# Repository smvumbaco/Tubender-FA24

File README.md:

# <PROJECT NAME>
<ADD BLURB ABOUT PROJECT>

## Directory Structure:
```
.
|
|───production  # contains files needed for final prototype
|   |
|   |───eCAD    # contains the KiCAD project
|   └───src     # contains the code needed for deployment
|
|───testing     # contains files relevant to testing components
|
└───README.md   # this file!
```

## Preferred Tools
- KiCAD 7 for PCB development
- Visual Studio Code / PlatformIO for code development
- Git CLI / GitHub Desktop for managing Git

## Branches
- Main branch contains all tested/verified work
- Development work is contained on separate branches

## References
- Schematics + Components (WIP)

## Practice Good Git Hygiene!
1. Only commit files you intended to change
2. Create branches for each feature
3. Check your branch before starting work
4. Pull frequently to avoid conflicts
5. Make Pull Requests when you are ready to merge into a larger branch

## Git Resources

* [Setting up Git](https://fanatical-colossus-434.notion.site/Git-Installation-and-Setup-d07b7d1ab5544424876f9fd3b4a0b312)
* [Intro to Git Crash Course](https://fanatical-colossus-434.notion.site/Crash-Course-Intro-to-Git-809641611da9478b8f9cca8fd97e49fe)

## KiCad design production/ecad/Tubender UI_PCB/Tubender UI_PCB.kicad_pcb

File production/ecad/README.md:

This is where all KiCAD stuff is stored

To make development and merging easier, a hierarchical design is suggested for schematics. This enables engineers to work on different sections of the schematicand minimize the amount of conflicts received.

`components` directory contains components utilized in this system

Please utilize whatever KiCAD version is requested by the lead. If you aren't sure which version, please ask your lead.

! Remember to only commit the `.kicad_sch`, `.kicad_pcb`, and `.kicad_pro` to this repository, everything else isn't needed to reconstruct the schematic on any KiCAD enabled machine

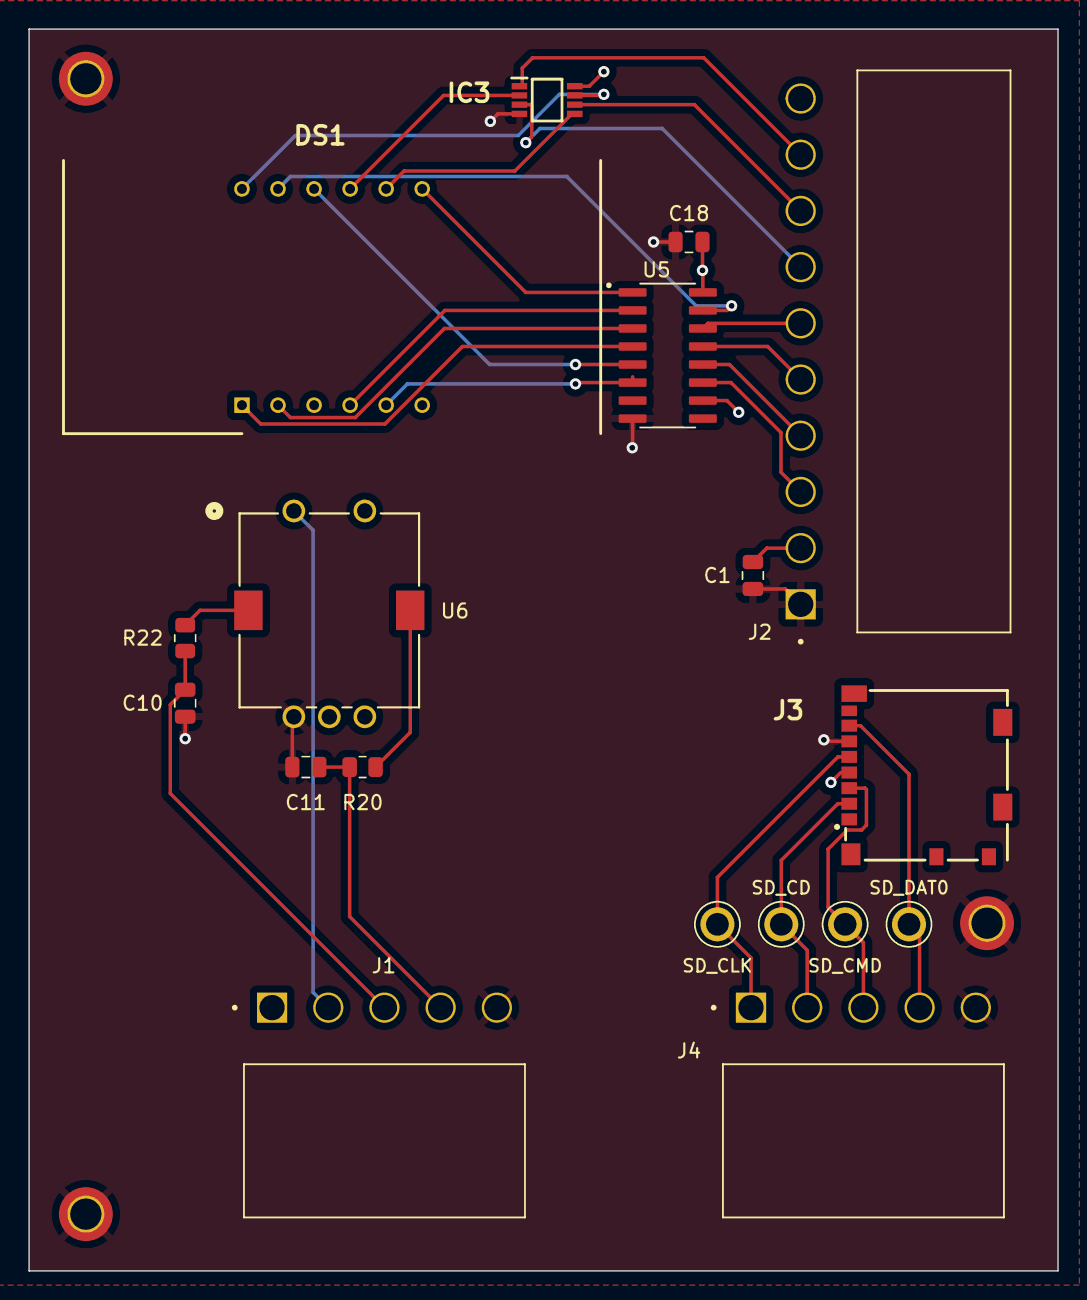
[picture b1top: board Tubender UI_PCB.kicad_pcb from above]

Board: 4 copper layers, 72.5 x 87.5 mm, 18 parts (0 on the bottom side), 29 nets.

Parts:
C1: 0.1u; C_0805_2012Metric
C10, C11: 0.01u; C_0805_2012Metric
C18: 0.1uF; C_0805_2012Metric
DS1: BC56-12EWA; DIPS1524W50P254L3760H835Q12N
IC3: SN74LVC1G29DCTR; SOP65P400X130-8N
J1, J4: 640387-5; TE_640387-5
J2: 1-640387-0; TE_1-640387-0
J3: 104031-0811; 1040310811
R20, R22: 10k; R_0805_2012Metric
SD_CD: 5006; KEYSTONE_5006
SD_CLK: 5006; KEYSTONE_5006
SD_CMD: 5006; KEYSTONE_5006
SD_DAT0: 5006; KEYSTONE_5006
U5: 74HC595; SOIC127P600X175-16N
U6: PEC11R-4215K-S0024; SW_PEC11R-4XXXK-SXXXX_BRN

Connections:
7-SEG_A0: IC3.3 (A0), J2.7
7-SEG_A1: IC3.6 (A1), J2.8
7-SEG_Gb: IC3.1 (~G), J2.9
7-SEG_OEb: J2.5, U5.13 (~OE)
7-SEG_RCLK: J2.4, U5.12 (RCLK)
7-SEG_SER: J2.6, U5.14 (SER)
7-SEG_SRCLK: J2.3, U5.11 (SRCLK)
+3V3: C1.1, J2.2, J3.4 (VDD), U5.10 (~SRCLR)
+5V: C18.1, IC3.8 (VCC), J1.1, J2.10, U5.16 (VCC), U6.2
DIAL_BUTTON: J1.2, U6.1
DIAL_CHANNEL_A: C10.1, J1.3, R22.2
DIAL_CHANNEL_B: C11.1, J1.4, R20.2
GND: C1.2, C10.2, C11.2, C18.2, IC3.4 (GND), J1.5, J2.1, J3.6 (VSS), J4.5, U5.8 (GND), U6.5 (C)
unnamed: DS1.11 (ANODE_A), U5.15 (QA)
unnamed: DS1.7 (ANODE_B), U5.1 (QB)
unnamed: DS1.4 (ANODE_C), U5.2 (QC)
unnamed: DS1.2 (ANODE_D), U5.3 (QD)
unnamed: DS1.1 (ANODE_E), U5.4 (QE)
unnamed: DS1.10 (ANODE_F), U5.5 (QF)
unnamed: DS1.5 (ANODE_G), U5.6 (QG)
unnamed: DS1.12 (COMMON_CATHODE_DIG1), IC3.7 (Y0)
unnamed: DS1.9 (COMMON_CATHODE_DIG2), IC3.2 (Y1)
unnamed: DS1.8 (COMMON_CATHODE_DIG_3), IC3.5 (Y2)
unnamed: R22.1, U6.3 (A)
unnamed: R20.1, U6.4 (B)
SD_CD: J3.2 (CD/DAT3), J4.2, SD_CD.TP
SD_CLK: J3.5 (CLK), J4.1, SD_CLK.TP
SD_CMD: J3.3 (CMD), J4.3, SD_CMD.TP
SD_DAT0: J3.7 (DAT0), J4.4, SD_DAT0.TP

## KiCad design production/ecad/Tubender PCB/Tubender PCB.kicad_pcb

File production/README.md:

# Production
This directory is for code/schematics/layouts that will be implemented in the final prototype.

> **_NOTE:_** If you have code to test out a component/subsystem, it should probably go into ```/testing```

## Directory Structure:
```
.
|───ecad    # contains any schematic/board development files
|
└───src     # contains any embedded code or important scripts
```

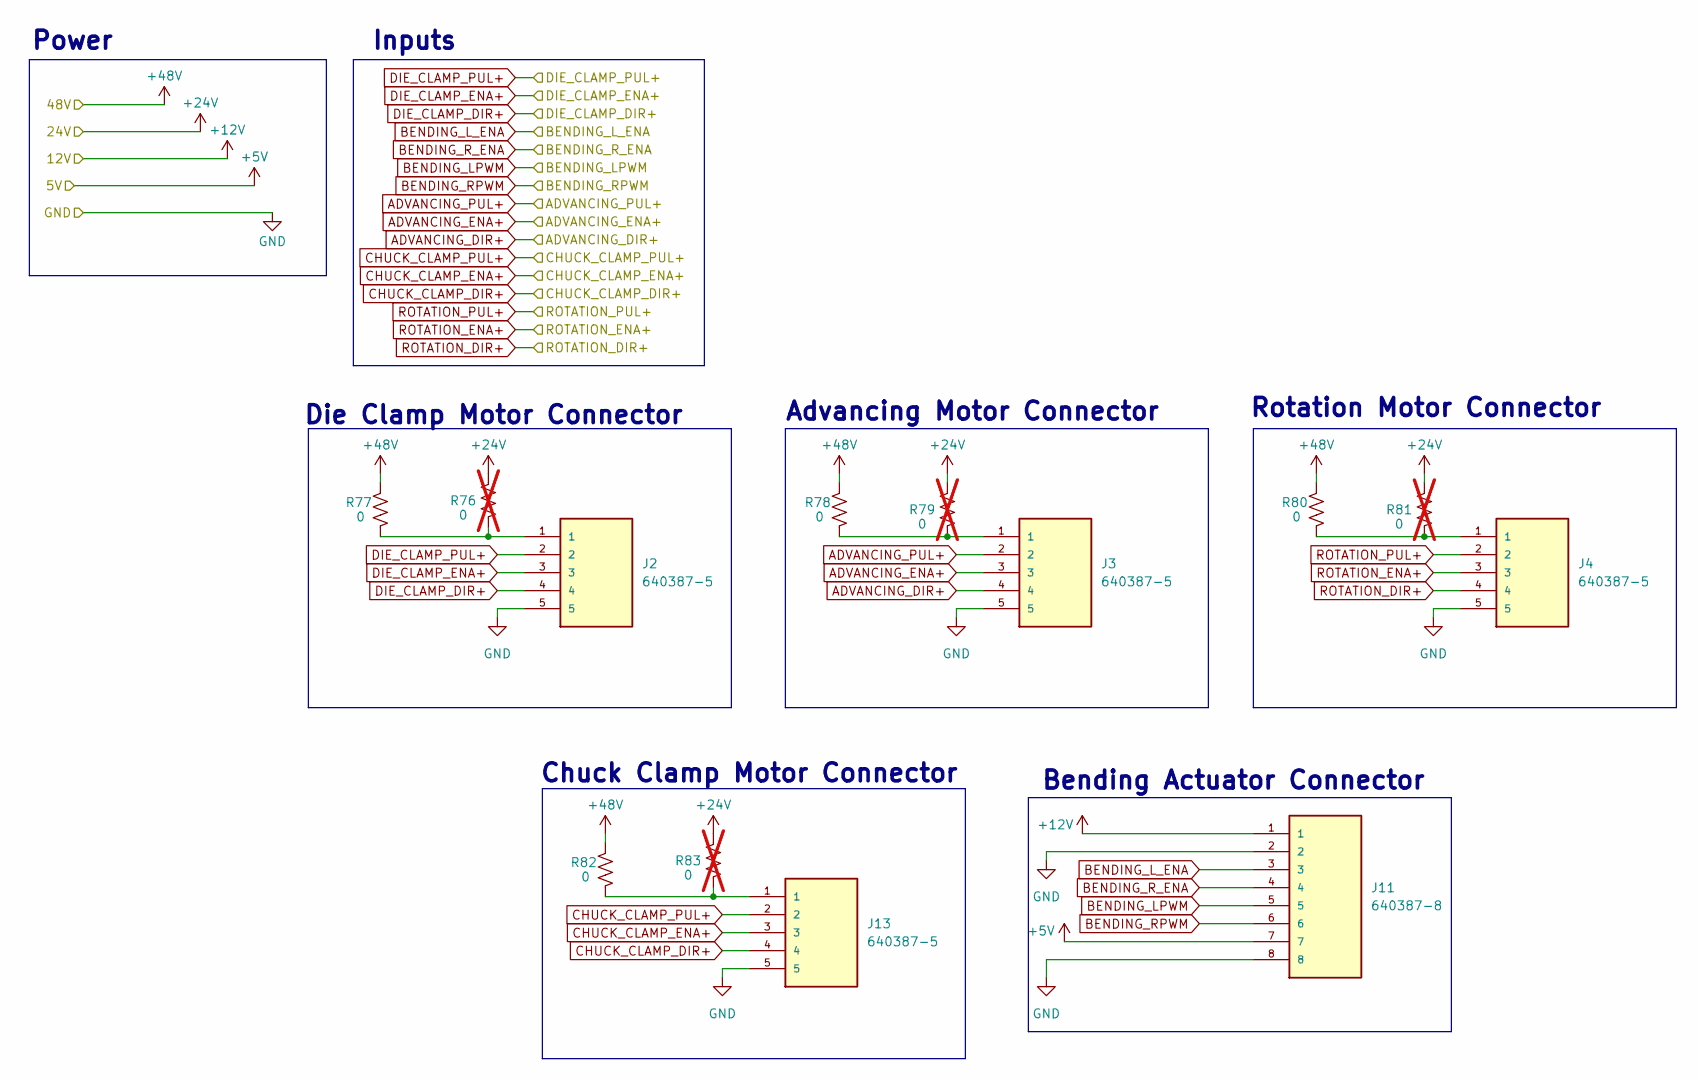
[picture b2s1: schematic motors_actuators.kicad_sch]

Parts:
J2, J3, J4, J13: 640387-5; TE_640387-5; PARTREV R
J11: 640387-8; TE_640387-8; PARTREV R
R76, R79, R81, R83: 0; R_0805_2012Metric; not fitted
R77, R78, R80, R82: 0; R_0805_2012Metric

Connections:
5V: J11.7; also elsewhere on the board
12V: J11.1; also elsewhere on the board
24V: R76.2, R79.2, R81.2, R83.2; also elsewhere on the board
48V: R77.2, R78.2, R80.2, R82.2; also elsewhere on the board
ADVANCING_DIR+: J3.4; also elsewhere on the board
ADVANCING_ENA+: J3.3; also elsewhere on the board
ADVANCING_PUL+: J3.2; also elsewhere on the board
BENDING_LPWM: J11.5; also elsewhere on the board
BENDING_L_ENA: J11.3; also elsewhere on the board
BENDING_RPWM: J11.6; also elsewhere on the board
BENDING_R_ENA: J11.4; also elsewhere on the board
CHUCK_CLAMP_DIR+: J13.4; also elsewhere on the board
CHUCK_CLAMP_ENA+: J13.3; also elsewhere on the board
CHUCK_CLAMP_PUL+: J13.2; also elsewhere on the board
DIE_CLAMP_DIR+: J2.4; also elsewhere on the board
DIE_CLAMP_ENA+: J2.3; also elsewhere on the board
DIE_CLAMP_PUL+: J2.2; also elsewhere on the board
GND: J2.5, J3.5, J4.5, J11.2, J11.8, J13.5; also elsewhere on the board
unnamed: J2.1, R76.1, R77.1
unnamed: J3.1, R78.1, R79.1
unnamed: J4.1, R80.1, R81.1
unnamed: J13.1, R82.1, R83.1
ROTATION_DIR+: J4.4; also elsewhere on the board
ROTATION_ENA+: J4.3; also elsewhere on the board
ROTATION_PUL+: J4.2; also elsewhere on the board

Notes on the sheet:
Chuck Clamp Motor Connector
Die Clamp Motor Connector
Bending Actuator Connector
Inputs
Advancing Motor Connector
Power
Rotation Motor Connector

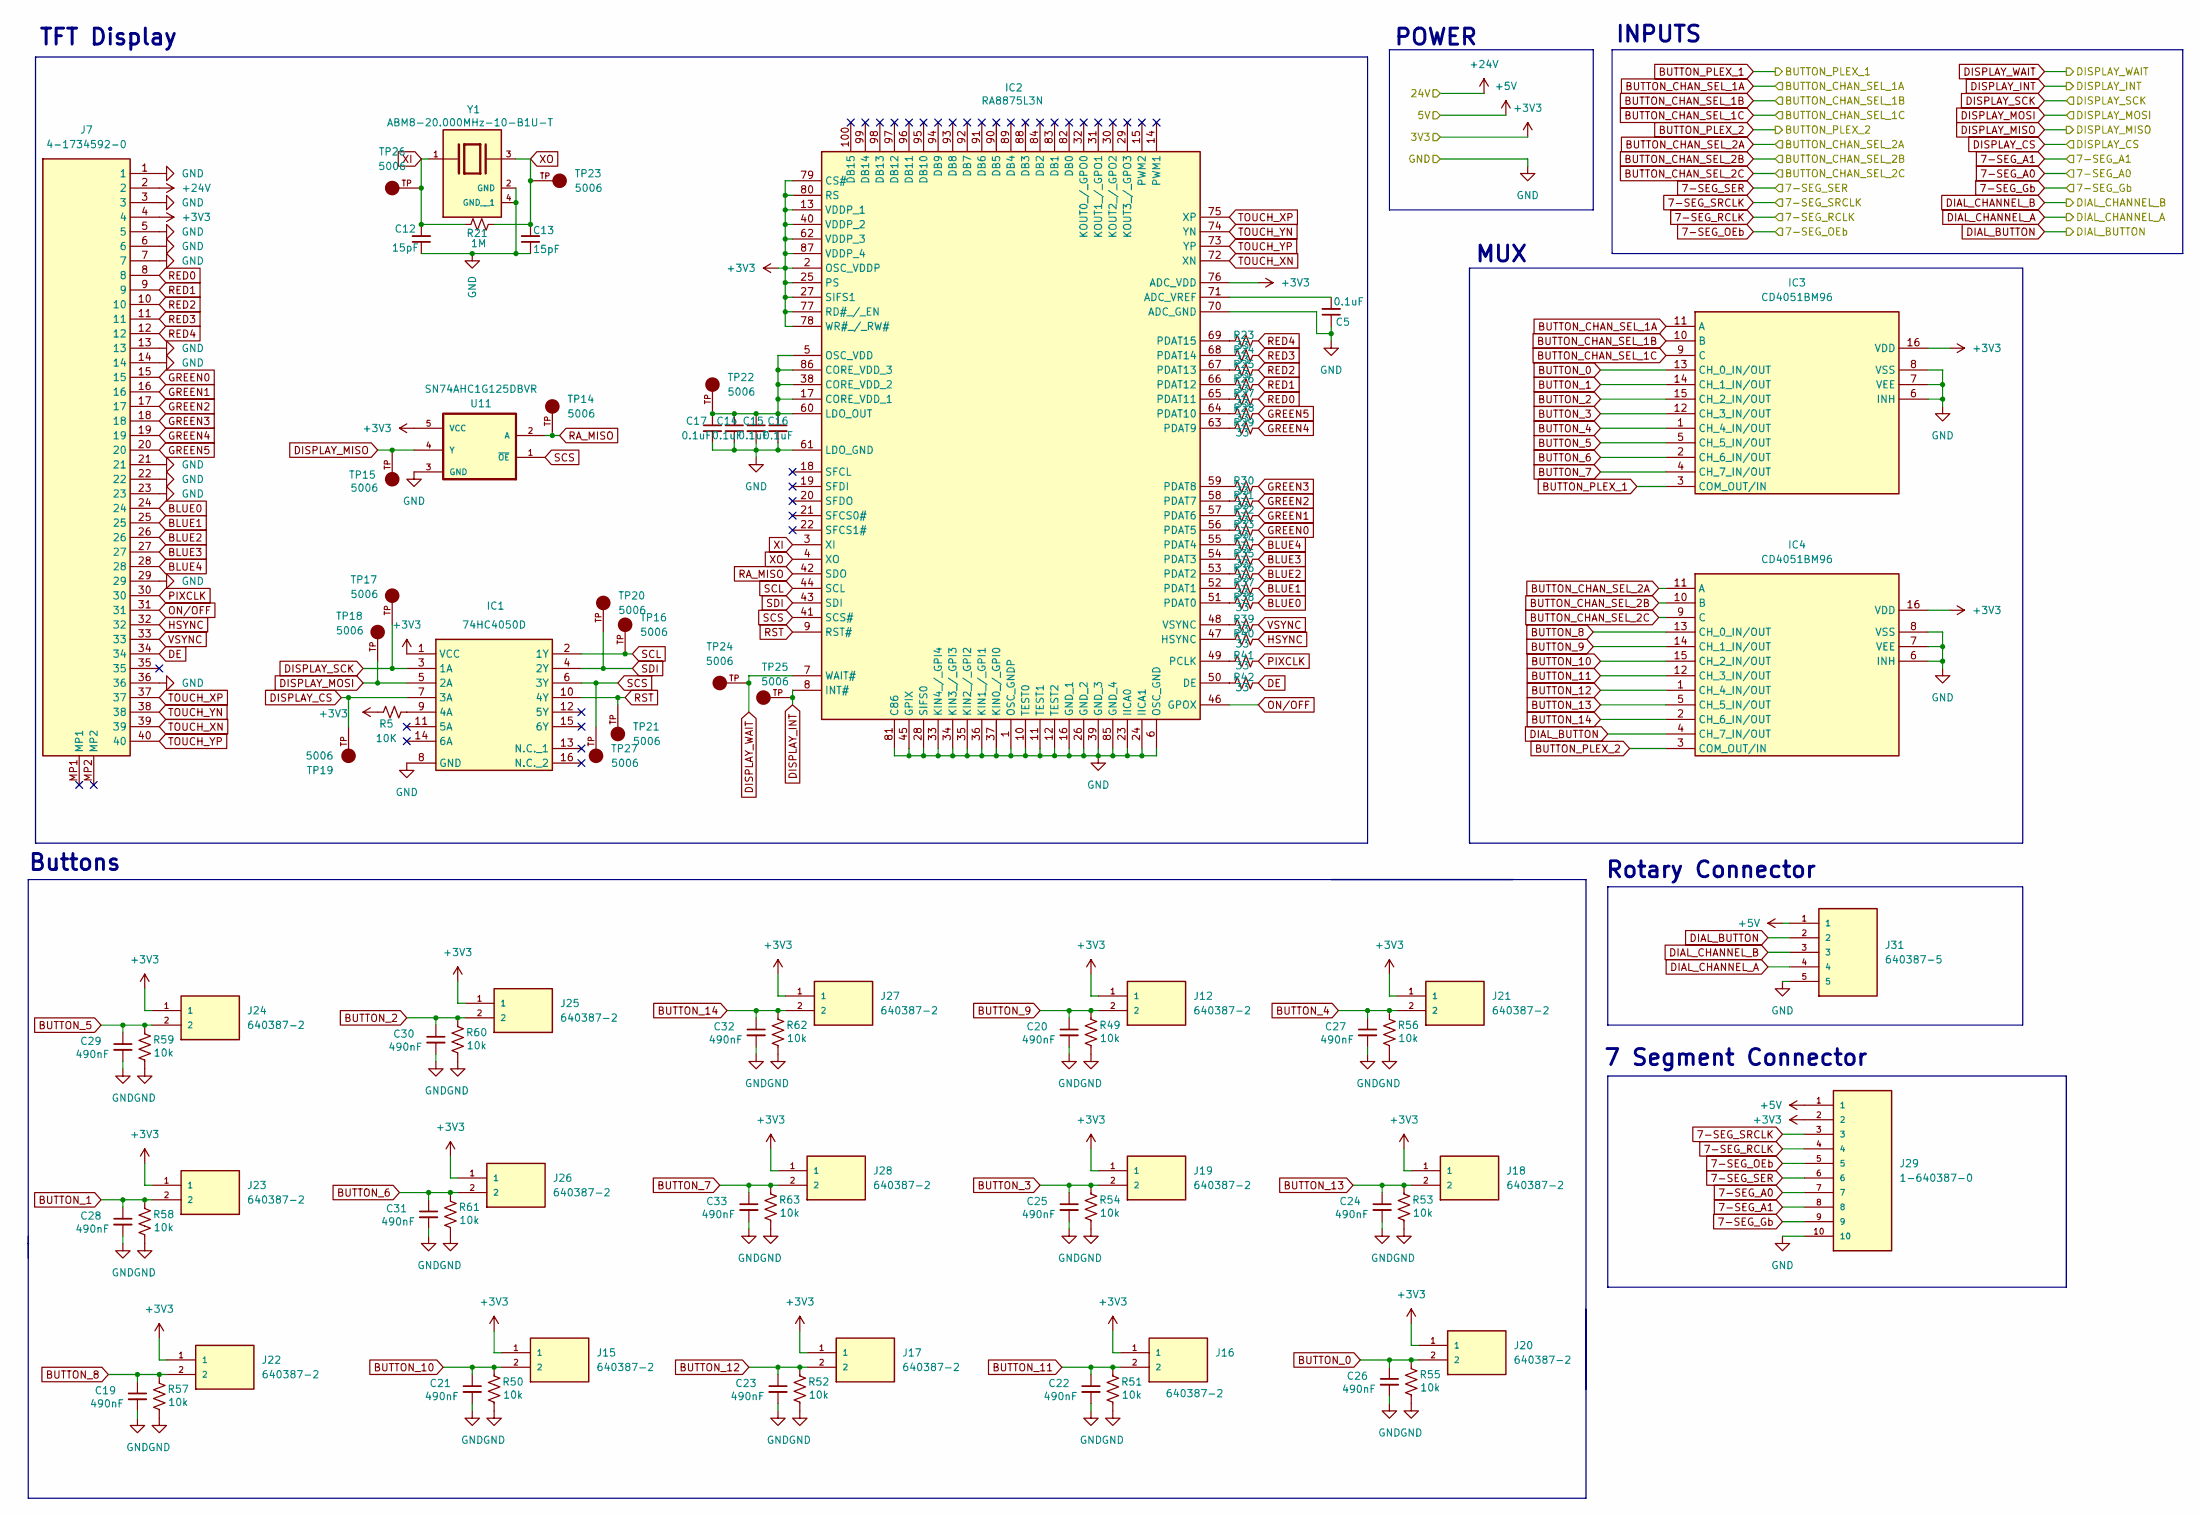
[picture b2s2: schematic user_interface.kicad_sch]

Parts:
C5, C14, C15, C16, C17: 0.1uF; C_0805_2012Metric
C12, C13: 15pF; C_0805_2012Metric
C19, C20, C21, C22, C23, C24, C25, C26, C27, C28, C29, C30, C31, C32, C33: 490nF; C_0805_2012Metric
IC1: 74HC4050D; SOT109-1_NXP; Manufacturer_Part_Number 74HC4050D; Mouser Part Number 771-74HC4050D
IC2: RA8875L3N; QFP50P1600X1600X160-100N; Manufacturer_Part_Number RA8875L3N
IC3, IC4: CD4051BM96; SOIC127P600X175-16N; Manufacturer_Part_Number CD4051BM96; Mouser Part Number 595-CD4051BM96
J7: 4-1734592-0; TE_4-1734592-0; Manufacturer_Part_Number 4-1734592-0; Mouser Part Number 571-4-1734592-0
J12, J15, J16, J17, J18, J19, J20, J21, J22, J23, J24, J25, J26, J27, J28: 640387-2; TE_640387-2; PARTREV R
J29: 1-640387-0; TE_1-640387-0; PARTREV R
J31: 640387-5; TE_640387-5; PARTREV R
R5: 10K; R_0805_2012Metric
R21: 1M; R_0805_2012Metric
R23, R24, R25, R26, R27, R28, R29, R30, R31, R32, R33, R34, R35, R36, R37, R38, R39, R40, R41, R42: 33; R_0805_2012Metric
R49, R50, R51, R52, R53, R54, R55, R56, R57, R58, R59, R60, R61, R62, R63: 10k; R_0805_2012Metric
TP14, TP15, TP16, TP17, TP18, TP19, TP20, TP21, TP22, TP23, TP24, TP25, TP26, TP27: 5006; KEYSTONE_5006; PARTREV F
U11: SN74AHC1G125DBVR; SOT95P280X145-5N
Y1: ABM8-20.000MHz-10-B1U-T; XTAL_ABM8-20.000MHz-10-B1U-T; PARTREV 44041

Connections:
3.3V: IC1.1 (VCC), IC2.2 (OSC_VDDP), IC2.13 (VDDP_1), IC2.25 (PS), IC2.27 (SIFS1), IC2.40 (VDDP_2), IC2.62 (VDDP_3), IC2.76 (ADC_VDD), IC2.77 (RD#_/_EN), IC2.78 (WR#_/_RW#), IC2.79 (CS#), IC2.80 (RS), IC2.87 (VDDP_4), IC3.16 (VDD), IC4.16 (VDD), J7.4, J12.1, J15.1, J16.1, J17.1, J18.1, J19.1, J20.1, J21.1, J22.1, J23.1, J24.1, J25.1, J26.1, J27.1, J28.1, J29.2, R5.2, U11.5 (VCC); also elsewhere on the board
5V: J29.1, J31.1; also elsewhere on the board
7-SEG_A0: J29.7; also elsewhere on the board
7-SEG_A1: J29.8; also elsewhere on the board
7-SEG_Gb: J29.9; also elsewhere on the board
7-SEG_OEb: J29.5; also elsewhere on the board
7-SEG_RCLK: J29.4; also elsewhere on the board
7-SEG_SER: J29.6; also elsewhere on the board
7-SEG_SRCLK: J29.3; also elsewhere on the board
24V: J7.2; also elsewhere on the board
BLUE0: J7.24, R38.2
BLUE1: J7.25, R37.2
BLUE2: J7.26, R36.2
BLUE3: J7.27, R35.2
BLUE4: J7.28, R34.2
BUTTON_0: C26.1, IC3.13 (CH_0_IN/OUT), J20.2, R55.2
BUTTON_1: C28.1, IC3.14 (CH_1_IN/OUT), J23.2, R58.2
BUTTON_2: C30.1, IC3.15 (CH_2_IN/OUT), J25.2, R60.2
BUTTON_3: C25.1, IC3.12 (CH_3_IN/OUT), J19.2, R54.2
BUTTON_4: C27.1, IC3.1 (CH_4_IN/OUT), J21.2, R56.2
BUTTON_5: C29.1, IC3.5 (CH_5_IN/OUT), J24.2, R59.2
BUTTON_6: C31.1, IC3.2 (CH_6_IN/OUT), J26.2, R61.2
BUTTON_7: C33.1, IC3.4 (CH_7_IN/OUT), J28.2, R63.2
BUTTON_8: C19.1, IC4.13 (CH_0_IN/OUT), J22.2, R57.2
BUTTON_9: C20.1, IC4.14 (CH_1_IN/OUT), J12.2, R49.2
BUTTON_10: C21.1, IC4.15 (CH_2_IN/OUT), J15.2, R50.2
BUTTON_11: C22.1, IC4.12 (CH_3_IN/OUT), J16.2, R51.2
BUTTON_12: C23.1, IC4.1 (CH_4_IN/OUT), J17.2, R52.2
BUTTON_13: C24.1, IC4.5 (CH_5_IN/OUT), J18.2, R53.2
BUTTON_14: C32.1, IC4.2 (CH_6_IN/OUT), J27.2, R62.2
BUTTON_CHAN_SEL_1A: IC3.11 (A); also elsewhere on the board
BUTTON_CHAN_SEL_1B: IC3.10 (B); also elsewhere on the board
BUTTON_CHAN_SEL_1C: IC3.9 (C); also elsewhere on the board
BUTTON_CHAN_SEL_2A: IC4.11 (A); also elsewhere on the board
BUTTON_CHAN_SEL_2B: IC4.10 (B); also elsewhere on the board
BUTTON_CHAN_SEL_2C: IC4.9 (C); also elsewhere on the board
BUTTON_PLEX_1: IC3.3 (COM_OUT/IN); also elsewhere on the board
BUTTON_PLEX_2: IC4.3 (COM_OUT/IN); also elsewhere on the board
DE: J7.34, R42.2
DIAL_BUTTON: IC4.4 (CH_7_IN/OUT), J31.2
DIAL_CHANNEL_A: J31.4; also elsewhere on the board
DIAL_CHANNEL_B: J31.3; also elsewhere on the board
DISPLAY_CS: IC1.7 (3A), TP19.TP; also elsewhere on the board
DISPLAY_INT: IC2.8 (INT#), TP25.TP; also elsewhere on the board
DISPLAY_MISO: TP15.TP, U11.4 (Y); also elsewhere on the board
DISPLAY_MOSI: IC1.5 (2A), TP18.TP; also elsewhere on the board
DISPLAY_SCK: IC1.3 (1A), TP17.TP; also elsewhere on the board
DISPLAY_WAIT: IC2.7 (WAIT#), TP24.TP; also elsewhere on the board
GND: C5.1, C12.1, C13.1, C14.2, C15.2, C16.2, C17.2, C19.2, C20.2, C21.2, C22.2, C23.2, C24.2, C25.2, C26.2, C27.2, C28.2, C29.2, C30.2, C31.2, C32.2, C33.2, IC1.8 (GND), IC2.1 (OSC_GNDP), IC2.6 (OSC_GND), IC2.10 (TEST0), IC2.11 (TEST1), IC2.12 (TEST2), IC2.16 (GND_1), IC2.23 (IICA0), IC2.24 (IICA1), IC2.26 (GND_2), IC2.28 (SIFS0), IC2.33 (KIN4_/_GPI4), IC2.34 (KIN3_/_GPI3), IC2.35 (KIN2_/_GPI2), IC2.36 (KIN1_/_GPI1), IC2.37 (KIN0_/_GPI0), IC2.39 (GND_3), IC2.45 (GPIX), IC2.61 (LDO_GND), IC2.70 (ADC_GND), IC2.81 (C86), IC2.85 (GND_4), IC3.6 (INH), IC3.7 (VEE), IC3.8 (VSS), IC4.6 (INH), IC4.7 (VEE), IC4.8 (VSS), J7.1, J7.3, J7.5, J7.6, J7.7, J7.13, J7.14, J7.21, J7.22, J7.23, J7.29, J7.36, J29.10, J31.5, R49.1, R50.1, R51.1, R52.1, R53.1, R54.1, R55.1, R56.1, R57.1, R58.1, R59.1, R60.1, R61.1, R62.1, R63.1, U11.3 (GND), Y1.2 (GND), Y1.4 (GND__1); also elsewhere on the board
GREEN0: J7.15, R33.2
GREEN1: J7.16, R32.2
GREEN2: J7.17, R31.2
GREEN3: J7.18, R30.2
GREEN4: J7.19, R29.2
GREEN5: J7.20, R28.2
HSYNC: J7.32, R40.2
unnamed: IC1.9 (4A), R5.1
unnamed: C5.2, IC2.71 (ADC_VREF)
unnamed: C14.1, C15.1, C16.1, C17.1, IC2.5 (OSC_VDD), IC2.17 (CORE_VDD_1), IC2.38 (CORE_VDD_2), IC2.60 (LDO_OUT), IC2.86 (CORE_VDD_3), TP22.TP
unnamed: IC2.50 (DE), R42.1
unnamed: IC2.47 (HSYNC), R40.1
unnamed: IC2.49 (PCLK), R41.1
unnamed: IC2.51 (PDAT0), R38.1
unnamed: IC2.52 (PDAT1), R37.1
unnamed: IC2.53 (PDAT2), R36.1
unnamed: IC2.54 (PDAT3), R35.1
unnamed: IC2.55 (PDAT4), R34.1
unnamed: IC2.56 (PDAT5), R33.1
unnamed: IC2.57 (PDAT6), R32.1
unnamed: IC2.58 (PDAT7), R31.1
unnamed: IC2.59 (PDAT8), R30.1
unnamed: IC2.63 (PDAT9), R29.1
unnamed: IC2.64 (PDAT10), R28.1
unnamed: IC2.65 (PDAT11), R27.1
unnamed: IC2.66 (PDAT12), R26.1
unnamed: IC2.67 (PDAT13), R25.1
unnamed: IC2.68 (PDAT14), R24.1
unnamed: IC2.69 (PDAT15), R23.1
unnamed: IC2.48 (VSYNC), R39.1
ON/OFF: IC2.46 (GPOX), J7.31
PIXCLK: J7.30, R41.2
RA_MISO: IC2.42 (SDO), TP14.TP, U11.2 (A)
RED0: J7.8, R27.2
RED1: J7.9, R26.2
RED2: J7.10, R25.2
RED3: J7.11, R24.2
RED4: J7.12, R23.2
RST: IC1.10 (4Y), IC2.9 (RST#), TP21.TP
SCL: IC1.2 (1Y), IC2.44 (SCL), TP16.TP
SCS: IC1.6 (3Y), IC2.41 (SCS#), TP27.TP, U11.1 (~OE)
SDI: IC1.4 (2Y), IC2.43 (SDI), TP20.TP
TOUCH_XN: IC2.72 (XN), J7.39
TOUCH_XP: IC2.75 (XP), J7.37
TOUCH_YN: IC2.74 (YN), J7.38
TOUCH_YP: IC2.73 (YP), J7.40
VSYNC: J7.33, R39.2
XI: C12.2, IC2.3 (XI), R21.1, TP26.TP, Y1.1
XO: C13.2, IC2.4 (XO), R21.2, TP23.TP, Y1.3

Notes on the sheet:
INPUTS
POWER
TFT Display
MUX
7 Segment Connector
Rotary Connector
Buttons

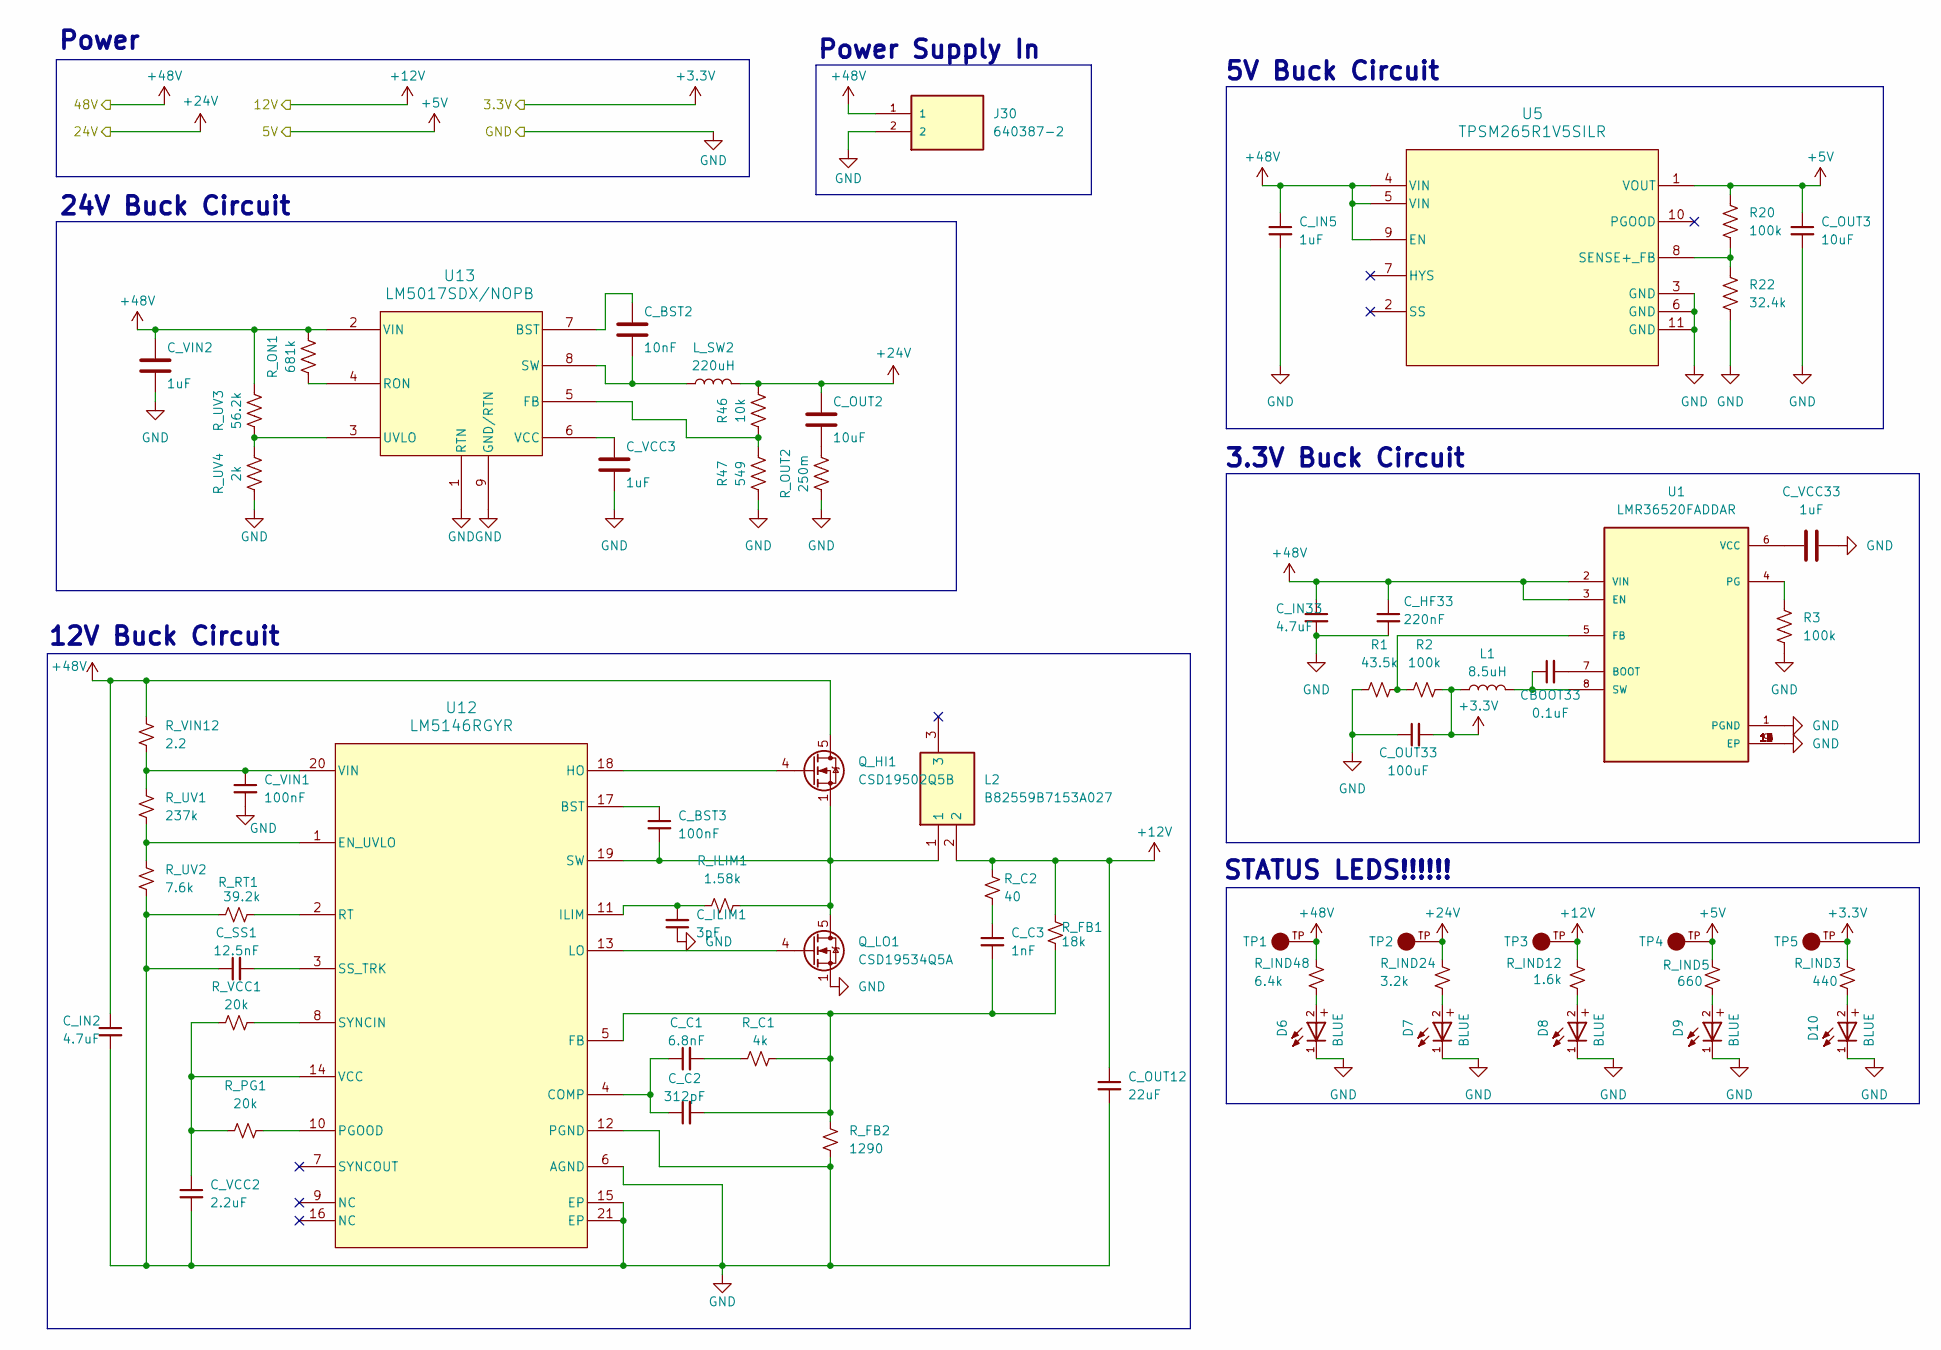
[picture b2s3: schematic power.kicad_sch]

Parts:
CBOOT33: 0.1uF; C_0805_2012Metric
C_BST2: 10nF; C_0805_2012Metric
C_BST3: 100nF; C_0805_2012Metric
C_C1: 6.8nF; C_0805_2012Metric
C_C2: 312pF; C_0805_2012Metric
C_C3: 1nF; C_0805_2012Metric
C_HF33: 220nF; C_0805_2012Metric
C_ILIM1: 3pF; C_0805_2012Metric
C_IN2, C_IN33: 4.7uF; C_0805_2012Metric
C_IN5: 1uF; C_0805_2012Metric
C_OUT2, C_OUT3: 10uF; C_0805_2012Metric
C_OUT12: 22uF; C_0805_2012Metric
C_OUT33: 100uF; C_1210_3225Metric
C_SS1: 12.5nF; C_0805_2012Metric
C_VCC2: 2.2uF; C_0805_2012Metric
C_VCC3, C_VCC33: 1uF; C_0805_2012Metric
C_VIN1: 100nF; C_0805_2012Metric
C_VIN2: 1uF; C_0805_2012Metric
D6, D7, D8, D9, D10: BLUE; WL-SMCW_0603
J30: 640387-2; TE_640387-2; PARTREV R
L1: 8.5uH; IND_BOURNS_5800
L2: B82559B7153A027; Mouser Part Number 871-B82559B7153A027
L_SW2: 220uH; SDR1006
Q_HI1: CSD19502Q5B; TDSON-8-1
Q_LO1: CSD19534Q5A; TDSON-8-1
R1: 43.5k; R_0805_2012Metric
R2, R3, R20: 100k; R_0805_2012Metric
R22: 32.4k; R_0805_2012Metric
R46: 10k; R_0805_2012Metric
R47: 549; R_0805_2012Metric
R_C1: 4k; R_0805_2012Metric
R_C2: 40; R_0805_2012Metric
R_FB1: 18k; R_0805_2012Metric
R_FB2: 1290; R_0805_2012Metric
R_ILIM1: 1.58k; R_0805_2012Metric
R_IND3: 440; R_0805_2012Metric
R_IND5: 660; R_0805_2012Metric
R_IND12: 1.6k; R_0805_2012Metric
R_IND24: 3.2k; R_0805_2012Metric
R_IND48: 6.4k; R_0805_2012Metric
R_ON1: 681k; R_0805_2012Metric
R_OUT2: 250m; R_0805_2012Metric
R_PG1: 20k; R_0805_2012Metric
R_RT1: 39.2k; R_0805_2012Metric
R_UV1: 237k; R_0805_2012Metric
R_UV2: 7.6k; R_0805_2012Metric
R_UV3: 56.2k; R_0805_2012Metric
R_UV4: 2k; R_0805_2012Metric
R_VCC1: 20k; R_0805_2012Metric
R_VIN12: 2.2; R_0805_2012Metric
TP1, TP2, TP3, TP4, TP5: 5006; KEYSTONE_5006; PARTREV F
U1: LMR36520FADDAR; IC_LMR36520FADDAR; PARTREV B
U5: TPSM265R1V5SILR; SIL0010C
U12: LM5146RGYR; RGY0020B-MFG
U13: LM5017SDX/NOPB; SDC08B

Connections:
3.3V: C_OUT33.2, L1.1, R2.2, R_IND3.1, TP5.TP; also elsewhere on the board
5V: C_OUT3.1, R20.2, R_IND5.1, TP4.TP, U5.1 (VOUT); also elsewhere on the board
12V: C_OUT12.1, L2.2, R_C2.1, R_FB1.1, R_IND12.1, TP3.TP; also elsewhere on the board
24V: C_OUT2.1, L_SW2.2, R46.2, R_IND24.1, TP2.TP; also elsewhere on the board
48V: C_HF33.1, C_IN2.1, C_IN5.1, C_IN33.1, C_VIN2.1, J30.1, Q_HI1.5 (D), R_IND48.1, R_ON1.2, R_UV3.2, R_VIN12.1, TP1.TP, U1.2 (VIN), U1.3 (EN), U5.4 (VIN), U5.5 (VIN), U5.9 (EN), U13.2 (VIN); also elsewhere on the board
GND: C_HF33.2, C_ILIM1.1, C_IN2.2, C_IN5.2, C_IN33.2, C_OUT3.2, C_OUT12.2, C_OUT33.1, C_SS1.1, C_VCC2.2, C_VCC3.2, C_VCC33.2, C_VIN1.2, C_VIN2.2, D6.1, D7.1, D8.1, D9.1, D10.1, J30.2, Q_LO1.1 (S), Q_LO1.2 (S), Q_LO1.3 (S), R1.1, R3.1, R22.1, R47.1, R_FB2.2, R_OUT2.1, R_RT1.1, R_UV2.2, R_UV4.1, U1.1 (PGND), U1.9 (EP), U1.10 (EP), U1.11 (EP), U1.12 (EP), U1.13 (EP), U1.14 (EP), U1.15 (EP), U5.3 (GND), U5.6 (GND), U5.11 (GND), U12.6 (AGND), U12.12 (PGND), U12.15 (EP), U12.21 (EP), U13.1 (RTN), U13.9 (GND/RTN); also elsewhere on the board
unnamed: C_C1.2, R_C1.1
unnamed: C_C3.1, R_C2.2
unnamed: C_OUT2.2, R_OUT2.2
unnamed: D6.2, R_IND48.2
unnamed: D7.2, R_IND24.2
unnamed: D8.2, R_IND12.2
unnamed: D9.2, R_IND5.2
unnamed: D10.2, R_IND3.2
unnamed: Q_HI1.4 (G), U12.18 (HO)
unnamed 141: C_BST3.2, L2.1, Q_HI1.1 (S), Q_HI1.2 (S), Q_HI1.3 (S), Q_LO1.5 (D), R_ILIM1.2, U12.19 (SW); also elsewhere on the board
unnamed: Q_LO1.4 (G), U12.13 (LO)
unnamed: CBOOT33.2, U1.7 (BOOT)
unnamed: R1.2, R2.1, U1.5 (FB)
unnamed: R3.2, U1.4 (PG)
unnamed: CBOOT33.1, L1.2, U1.8 (SW)
unnamed: C_VCC33.1, U1.6 (VCC)
unnamed: R20.1, R22.2, U5.8 (SENSE+_FB)
unnamed: C_BST3.1, U12.17 (BST)
unnamed: C_C1.1, C_C2.1, U12.4 (COMP)
unnamed: R_UV1.2, R_UV2.1, U12.1 (EN_UVLO)
unnamed: C_C2.2, C_C3.2, R_C1.2, R_FB1.2, R_FB2.1, U12.5 (FB)
unnamed: C_ILIM1.2, R_ILIM1.1, U12.11 (ILIM)
unnamed: R_PG1.2, U12.10 (PGOOD)
unnamed: R_RT1.2, U12.2 (RT)
unnamed: C_SS1.2, U12.3 (SS_TRK)
unnamed: R_VCC1.1, U12.8 (SYNCIN)
unnamed: C_VCC2.1, R_PG1.1, R_VCC1.2, U12.14 (VCC)
unnamed: C_VIN1.1, R_UV1.1, R_VIN12.2, U12.20 (VIN)
unnamed: C_BST2.1, U13.7 (BST)
unnamed: R46.1, R47.2, U13.5 (FB)
unnamed: R_ON1.1, U13.4 (RON)
unnamed: C_BST2.2, L_SW2.1, U13.8 (SW)
unnamed: R_UV3.1, R_UV4.2, U13.3 (UVLO)
unnamed: C_VCC3.1, U13.6 (VCC)

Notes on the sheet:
12V Buck Circuit
Power
STATUS LEDS!!!!!!
Power Supply In
24V Buck Circuit
3.3V Buck Circuit
5V Buck Circuit
